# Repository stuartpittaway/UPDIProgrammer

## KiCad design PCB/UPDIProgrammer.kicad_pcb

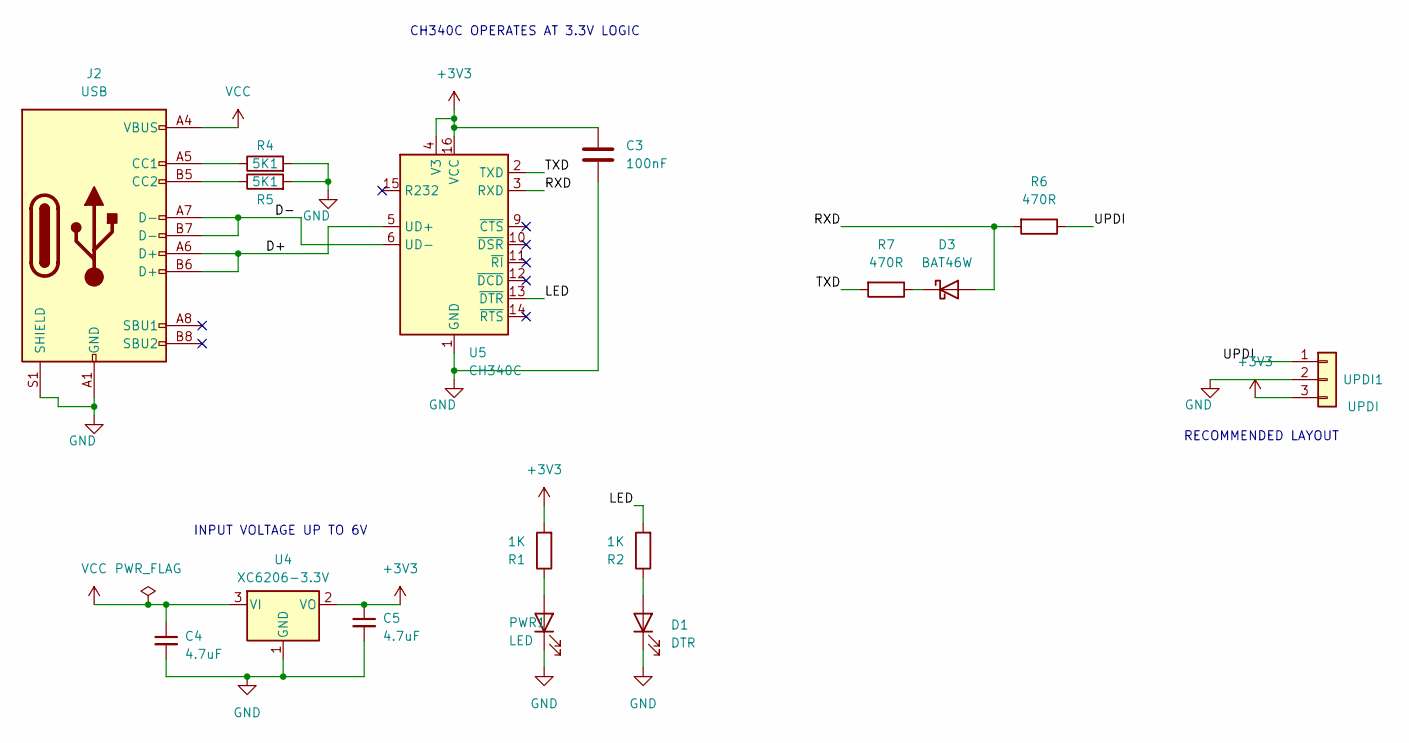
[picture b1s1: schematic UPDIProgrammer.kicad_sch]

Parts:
C3: 100nF; C_0805_2012Metric; PartNumber CC0805KRX7R9BB104; LCSCStockCode C49678
C4, C5: 4.7uF; C_0805_2012Metric; PartNumber CL21A475KAQNNNE; LCSCStockCode C1779
D1: DTR; LED_0805_2012Metric; PartNumber C2296; LCSCStockCode C2296
D3: BAT46W; D_SOD-123; PartNumber BAT46W; LCSCStockCode C54110
J2: USB; USB_C_Receptacle_G-Switch_GT-USB-7010ASV; PartNumber GT-USB-7010ASV; LCSCStockCode C2988369
PWR1: LED; LED_0805_2012Metric; PartNumber NCD0805R1; LCSCStockCode C84256
R1, R2: 1K; R_0805_2012Metric; PartNumber 0805W8F1001T5E; LCSCStockCode C17513
R4, R5: 5K1; R_0805_2012Metric; PartNumber 0805W8F5101T5E; LCSCStockCode C27834
R6: 470R; R_0805_2012Metric; PartNumber 0805W8F1001T5E; LCSCStockCode C17513
R7: 470R; R_0805_2012Metric
U4: XC6206-3.3V; SOT-23-3; PartNumber XC6206-3.3V; LCSCStockCode C2891841
U5: CH340C; SOIC-16_3.9x9.9mm_P1.27mm; PartNumber CH340C; LCSCStockCode C84681
UPDI1: UPDI; PinHeader_1x03_P2.54mm_Horizontal

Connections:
+3V3: C3.1, C5.1, R1.2, U4.2 (VO), U5.4 (V3), U5.16 (VCC), UPDI1.3
/D+: J2.A6 (D+), J2.B6 (D+), U5.5 (UD+)
/D-: J2.A7 (D-), J2.B7 (D-), U5.6 (UD-)
/LED: R2.2, U5.13 (~DTR)
/RXD: D3.2 (A), R6.2, U5.3 (RXD)
/TXD: R7.2, U5.2 (TXD)
/UPDI: R6.1, UPDI1.1
GND: C3.2, C4.2, C5.2, D1.1 (K), J2.A1 (GND), J2.A12 (GND), J2.B1 (GND), J2.B12 (GND), J2.S1 (SHIELD), PWR1.1 (K), R4.2, R5.2, U4.1 (GND), U5.1 (GND), UPDI1.2
unnamed: D1.2 (A), R2.1
unnamed: D3.1 (K), R7.1
unnamed: J2.A5 (CC1), R4.1
unnamed: J2.B5 (CC2), R5.1
unnamed: PWR1.2 (A), R1.1
VCC: C4.1, J2.A4 (VBUS), J2.A9 (VBUS), J2.B4 (VBUS), J2.B9 (VBUS), U4.3 (VI)

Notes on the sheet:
INPUT VOLTAGE UP TO 6V
CH340C OPERATES AT 3.3V LOGIC
RECOMMENDED LAYOUT

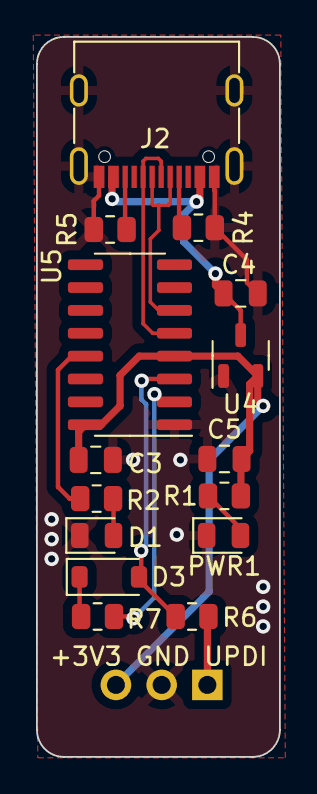
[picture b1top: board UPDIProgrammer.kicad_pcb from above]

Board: 2 copper layers, 13.5 x 40.0 mm, 16 parts (0 on the bottom side), 14 nets.

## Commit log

2023-12-05 Bump tj-actions/branch-names from 6 to 7.0.7 in /.github/workflows
    Bumps [tj-actions/branch-names](https://github.com/tj-actions/branch-names) from 6 to 7.0.7.
    - [Release notes](https://github.com/tj-actions/branch-names/releases)
    - [Changelog](https://github.com/tj-actions/branch-names/blob/main/HISTORY.md)
    - [Commits](https://github.com/tj-actions/branch-names/compare/v6...v7.0.7)
    ---
    updated-dependencies:
2025-07-25 Bump tj-actions/branch-names from 7.0.7 to 9.0.0 in /.github/workflows
    Bumps [tj-actions/branch-names](https://github.com/tj-actions/branch-names) from 7.0.7 to 9.0.0.
    - [Release notes](https://github.com/tj-actions/branch-names/releases)
    - [Changelog](https://github.com/tj-actions/branch-names/blob/main/HISTORY.md)
    - [Commits](https://github.com/tj-actions/branch-names/compare/v7.0.7...v9.0.0)
    ---
    updated-dependencies:
